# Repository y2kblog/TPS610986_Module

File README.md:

# TPS610986 超低消費電力 3.3V出力昇圧モジュール

<!--

-->

## 概要

超低消費電力の昇圧型DC-DCコンバータ TPS610986 (Texas Instruments Inc.製) を搭載したモジュールです。  
TPS610986の**静止電流は約1μA程度**（ローパワーモード時）と非常に低く、また**0.7Vから動作**するため、コイン電池1個、もしくはアルカリ／ニカド／ニッケル水素乾電池1～2本で駆動するアプリケーションに適しています。  
さらに、TPS610986は**ロードスイッチ機能付き**であり、MODEピンを利用することでVSUBピンのON/OFFの切り替えとローパワーモード（超低静止電流）／アクティブモード（高過渡応答）の選択が可能です。  
これにより、定期的にウェイクアップして動作し、それ以外の大半の時間はスリープするようなバッテリー駆動のアプリケーションにおいて、常時出力のVMAINピンをマイコン（MCU）に繋ぎ、VSUBピンをその他のサブシステム（センサ、GPS、無線モジュール、SDカード等）に接続すると、スリープ時はローパワーモードでマイコンのみに電力を供給することでバッテリー寿命を延ばし、動作時はアクティブモードでサブシステムにも高過渡応答の安定的な電力を供給する、といったことが可能です。  
<!--
TPS610986の静止電流は約1μA程度（ローパワーモード時）と非常に低いため、バッテリー駆動のアプリケーションに適しています。  
-->
<!--
スリープ時はローパワーモードでマイコンのみに電力を供給することでバッテリー寿命を延ばし、ウェイクアップ時はアクティブモードで良好な過渡応答を得ることができます。  
また、最大スイッチング電流は350mAであるため、SDカード等の比較的大電流を要するアプリケーションにも使用できます。
-->

### 仕様
- 入力電圧：0.7V～4.5V (※3.3V以上入力した場合はパススルーとなります)
- 出力電圧：3.3V (低負荷のバーストモード時：3.4V)
- 最大スイッチング電流：350mA (※最大出力電流は入力電圧と効率に依存します)
- ロードスイッチ付
- 効率
  - 88% (入力電圧2V～3.3V、負荷10μA、ローパワーモード時)
  - 93% (入力電圧2V～3.3V、負荷5mA～100mA)
- 基板サイズ：横12.7mm×縦10.0ｍｍ

## 販売  
[スイッチサイエンス委託販売ページ](https://www.switch-science.com/catalog/3659/)  
※大量注文や在庫に関する問い合わせは[こちら](mailto:info.y2kb@gmail.com)までご連絡ください。  

### 回路図  

### 寸法

## 性能評価  

### 静止電流  

### 整定時間  

#### VSUBピンの整定時間（負荷：無し）：約800μs

#### VSUBピンの整定時間（負荷：210mA）：約760μs

#### VMAINピンの整定時間（負荷：無し）：約580μs

#### VMAINピンの整定時間（負荷：210mA）：約1500μs

## データシート  
[TPS610986データシート(英語)](http://www.ti.com/lit/ds/symlink/tps610986.pdf)

## License
MIT License

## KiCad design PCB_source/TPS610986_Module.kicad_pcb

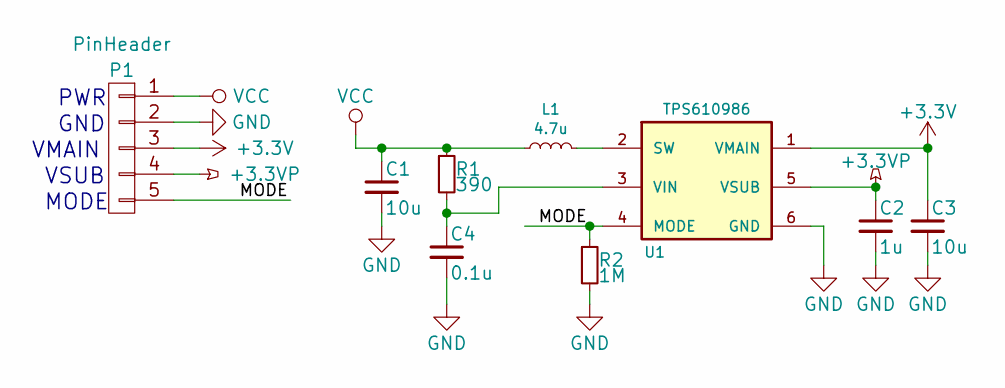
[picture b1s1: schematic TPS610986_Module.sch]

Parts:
C1, C3: 10u; C_0603
C2: 1u; C_0603
C4: 0.1u; C_0603
L1: 4.7u; USER_L_SPD3D16
P1: PinHeader; USER_SIL-5_NoSilk
R1: 390; R_0603
R2: 1M; R_0603
U1: TPS610986; USER_Boost_TPS61098x

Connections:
+3.3VP: C2.1, P1.4, U1.5 (VSUB)
+3V3: C3.1, P1.3, U1.1 (VMAIN)
/MODE: P1.5, R2.1, U1.4 (MODE)
GND: C1.2, C2.2, C3.2, C4.2, P1.2, R2.2, U1.6 (GND)
unnamed: C4.1, R1.2, U1.3 (VIN)
unnamed: L1.2, U1.2 (SW)
VCC: C1.1, L1.1, P1.1, R1.1

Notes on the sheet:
PWR
GND
VMAIN
VSUB
MODE

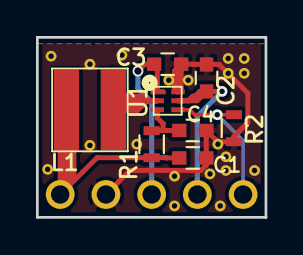
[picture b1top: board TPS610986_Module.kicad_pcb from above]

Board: 2 copper layers, 12.7 x 10.0 mm, 29 parts (0 on the bottom side), 7 nets.

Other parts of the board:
11, 12, 13, 14, 15, 21, 22, 23, 24, 25, 31, 32, 33, 34, 34#2, 35, 44, 45, 54, 55: USER_GNDvia

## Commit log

2018-01-10 :tada: Added .gitattributes & .gitignore files
2018-01-10 init
